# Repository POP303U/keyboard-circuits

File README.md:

# keyboard-circuits
Archive for arduino/pico-based keyboard pcbs

**WARNING!**

These board were created for learning purposes, I can't guarantee that these work!
The arduino-based boards use 'secret pins' that have to be used in order for all switches to work.
These circuits have to be to be correctly configured with QMK or these won't work!

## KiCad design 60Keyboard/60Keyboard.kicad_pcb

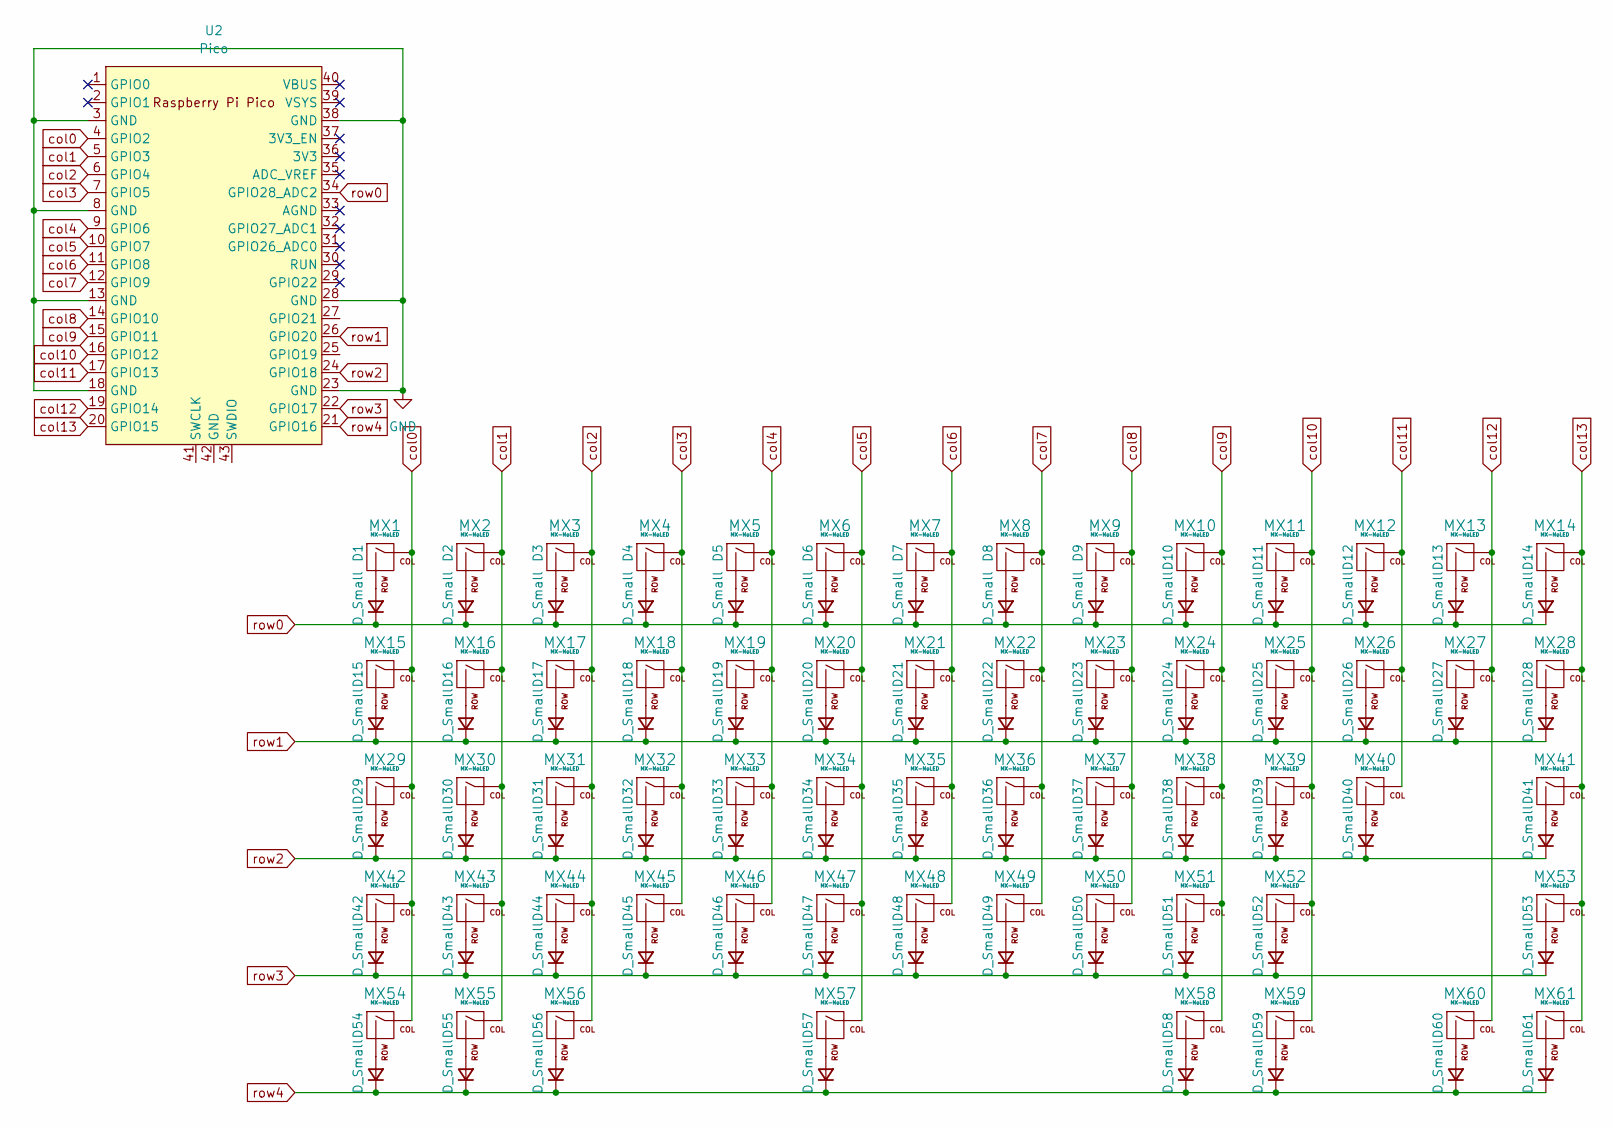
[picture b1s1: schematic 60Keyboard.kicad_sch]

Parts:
D1, D2, D3, D4, D5, D6, D7, D8, D9, D10, D11, D12, D13, D14, D15, D16, D17, D18, D19, D20, D21, D22, D23, D24, D25, D26, D27, D28, D29, D30, D31, D32, D33, D34, D35, D36, D37, D38, D39, D40, D41, D42, D43, D44, D45, D46, D47, D48, D49, D50, D51, D52, D53, D54, D55, D56, D57, D58, D59, D60, D61: D_Small; D_DO-41_SOD81_P10.16mm_Horizontal
MX1, MX2, MX3, MX4, MX5, MX6, MX7, MX8, MX9, MX10, MX11, MX12, MX13, MX16, MX17, MX18, MX19, MX20, MX21, MX22, MX23, MX24, MX25, MX26, MX27, MX30, MX31, MX32, MX33, MX34, MX35, MX36, MX37, MX38, MX39, MX40, MX43, MX44, MX45, MX46, MX47, MX48, MX49, MX50, MX51, MX52: MX-NoLED; MXOnly-1U-Hotswap
MX14: MX-NoLED; MXOnly-2U-Hotswap
MX15, MX28: MX-NoLED; MXOnly-1.5U-Hotswap
MX29: MX-NoLED; MXOnly-1.75U-Hotswap
MX41, MX42: MX-NoLED; MXOnly-2.25U-Hotswap
MX53: MX-NoLED; MXOnly-2.75U-Hotswap
MX54, MX55, MX56, MX58, MX59, MX60, MX61: MX-NoLED; MXOnly-1.25U-Hotswap
MX57: MX-NoLED; MXOnly-6.25U-Hotswap
U2: Pico; RPi_Pico_SMD_TH

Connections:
GND: U2.3 (GND), U2.8 (GND), U2.13 (GND), U2.18 (GND), U2.23 (GND), U2.28 (GND), U2.38 (GND)
unnamed: D1.2 (A), MX1.2 (ROW)
unnamed: D2.2 (A), MX2.2 (ROW)
unnamed: D3.2 (A), MX3.2 (ROW)
unnamed: D4.2 (A), MX4.2 (ROW)
unnamed: D5.2 (A), MX5.2 (ROW)
unnamed: D6.2 (A), MX6.2 (ROW)
unnamed: D7.2 (A), MX7.2 (ROW)
unnamed: D8.2 (A), MX8.2 (ROW)
unnamed: D9.2 (A), MX9.2 (ROW)
unnamed: D10.2 (A), MX10.2 (ROW)
unnamed: D11.2 (A), MX11.2 (ROW)
unnamed: D12.2 (A), MX12.2 (ROW)
unnamed: D13.2 (A), MX13.2 (ROW)
unnamed: D14.2 (A), MX14.2 (ROW)
unnamed: D15.2 (A), MX15.2 (ROW)
unnamed: D16.2 (A), MX16.2 (ROW)
unnamed: D17.2 (A), MX17.2 (ROW)
unnamed: D18.2 (A), MX18.2 (ROW)
unnamed: D19.2 (A), MX19.2 (ROW)
unnamed: D20.2 (A), MX20.2 (ROW)
unnamed: D21.2 (A), MX21.2 (ROW)
unnamed: D22.2 (A), MX22.2 (ROW)
unnamed: D23.2 (A), MX23.2 (ROW)
unnamed: D24.2 (A), MX24.2 (ROW)
unnamed: D25.2 (A), MX25.2 (ROW)
unnamed: D26.2 (A), MX26.2 (ROW)
unnamed: D27.2 (A), MX27.2 (ROW)
unnamed: D28.2 (A), MX28.2 (ROW)
unnamed: D29.2 (A), MX29.2 (ROW)
unnamed: D30.2 (A), MX30.2 (ROW)
unnamed: D31.2 (A), MX31.2 (ROW)
unnamed: D32.2 (A), MX32.2 (ROW)
unnamed: D33.2 (A), MX33.2 (ROW)
unnamed: D34.2 (A), MX34.2 (ROW)
unnamed: D35.2 (A), MX35.2 (ROW)
unnamed: D36.2 (A), MX36.2 (ROW)
unnamed: D37.2 (A), MX37.2 (ROW)
unnamed: D38.2 (A), MX38.2 (ROW)
unnamed: D39.2 (A), MX39.2 (ROW)
unnamed: D40.2 (A), MX40.2 (ROW)
unnamed: D41.2 (A), MX41.2 (ROW)
unnamed: D42.2 (A), MX42.2 (ROW)
unnamed: D43.2 (A), MX43.2 (ROW)
unnamed: D44.2 (A), MX44.2 (ROW)
unnamed: D45.2 (A), MX45.2 (ROW)
unnamed: D46.2 (A), MX46.2 (ROW)
unnamed: D47.2 (A), MX47.2 (ROW)
unnamed: D48.2 (A), MX48.2 (ROW)
unnamed: D49.2 (A), MX49.2 (ROW)
unnamed: D50.2 (A), MX50.2 (ROW)
unnamed: D51.2 (A), MX51.2 (ROW)
unnamed: D52.2 (A), MX52.2 (ROW)
unnamed: D53.2 (A), MX53.2 (ROW)
unnamed: D54.2 (A), MX54.2 (ROW)
unnamed: D55.2 (A), MX55.2 (ROW)
unnamed: D56.2 (A), MX56.2 (ROW)
unnamed: D57.2 (A), MX57.2 (ROW)
unnamed: D58.2 (A), MX58.2 (ROW)
unnamed: D59.2 (A), MX59.2 (ROW)
unnamed: D60.2 (A), MX60.2 (ROW)
unnamed: D61.2 (A), MX61.2 (ROW)
col0: MX1.1 (COL), MX15.1 (COL), MX29.1 (COL), MX42.1 (COL), MX54.1 (COL), U2.4 (GPIO2)
col1: MX2.1 (COL), MX16.1 (COL), MX30.1 (COL), MX43.1 (COL), MX55.1 (COL), U2.5 (GPIO3)
col2: MX3.1 (COL), MX17.1 (COL), MX31.1 (COL), MX44.1 (COL), MX56.1 (COL), U2.6 (GPIO4)
col3: MX4.1 (COL), MX18.1 (COL), MX32.1 (COL), MX45.1 (COL), U2.7 (GPIO5)
col4: MX5.1 (COL), MX19.1 (COL), MX33.1 (COL), MX46.1 (COL), U2.9 (GPIO6)
col5: MX6.1 (COL), MX20.1 (COL), MX34.1 (COL), MX47.1 (COL), MX57.1 (COL), U2.10 (GPIO7)
col6: MX7.1 (COL), MX21.1 (COL), MX35.1 (COL), MX48.1 (COL), U2.11 (GPIO8)
col7: MX8.1 (COL), MX22.1 (COL), MX36.1 (COL), MX49.1 (COL), U2.12 (GPIO9)
col8: MX9.1 (COL), MX23.1 (COL), MX37.1 (COL), MX50.1 (COL), U2.14 (GPIO10)
col9: MX10.1 (COL), MX24.1 (COL), MX38.1 (COL), MX51.1 (COL), MX58.1 (COL), U2.15 (GPIO11)
col10: MX11.1 (COL), MX25.1 (COL), MX39.1 (COL), MX52.1 (COL), MX59.1 (COL), U2.16 (GPIO12)
col11: MX12.1 (COL), MX26.1 (COL), MX40.1 (COL), U2.17 (GPIO13)
col12: MX13.1 (COL), MX27.1 (COL), MX60.1 (COL), U2.19 (GPIO14)
col13: MX14.1 (COL), MX28.1 (COL), MX41.1 (COL), MX53.1 (COL), MX61.1 (COL), U2.20 (GPIO15)
row0: D1.1 (K), D2.1 (K), D3.1 (K), D4.1 (K), D5.1 (K), D6.1 (K), D7.1 (K), D8.1 (K), D9.1 (K), D10.1 (K), D11.1 (K), D12.1 (K), D13.1 (K), D14.1 (K), U2.34 (GPIO28_ADC2)
row1: D15.1 (K), D16.1 (K), D17.1 (K), D18.1 (K), D19.1 (K), D20.1 (K), D21.1 (K), D22.1 (K), D23.1 (K), D24.1 (K), D25.1 (K), D26.1 (K), D27.1 (K), D28.1 (K), U2.26 (GPIO20)
row2: D29.1 (K), D30.1 (K), D31.1 (K), D32.1 (K), D33.1 (K), D34.1 (K), D35.1 (K), D36.1 (K), D37.1 (K), D38.1 (K), D39.1 (K), D40.1 (K), D41.1 (K), U2.24 (GPIO18)
row3: D42.1 (K), D43.1 (K), D44.1 (K), D45.1 (K), D46.1 (K), D47.1 (K), D48.1 (K), D49.1 (K), D50.1 (K), D51.1 (K), D52.1 (K), D53.1 (K), U2.22 (GPIO17)
row4: D54.1 (K), D55.1 (K), D56.1 (K), D57.1 (K), D58.1 (K), D59.1 (K), D60.1 (K), D61.1 (K), U2.21 (GPIO16)

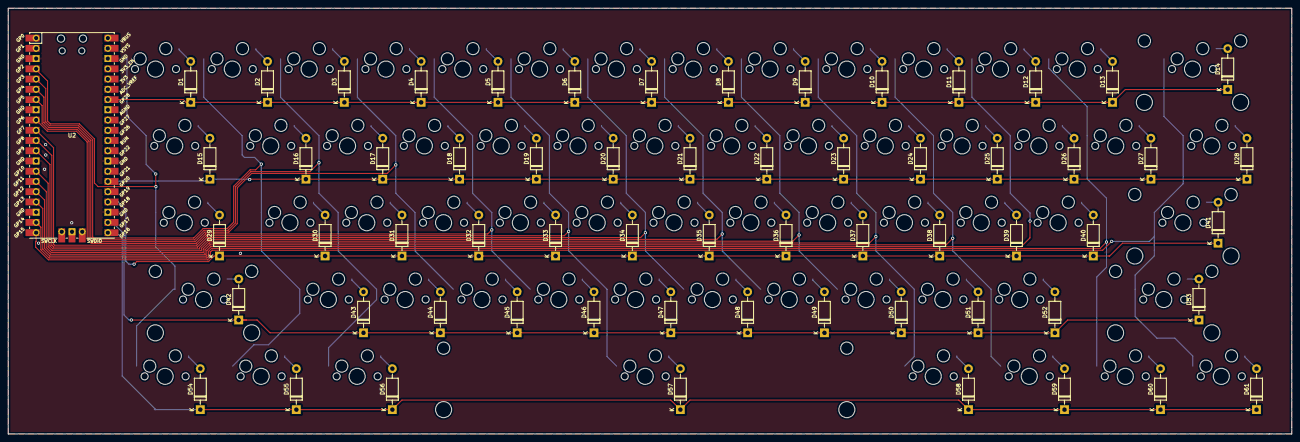
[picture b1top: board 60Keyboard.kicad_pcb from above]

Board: 2 copper layers, 318.3 x 105.6 mm, 123 parts (0 on the bottom side), 81 nets.

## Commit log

2023-06-01 added keyboards
2023-06-01 Added warnings
